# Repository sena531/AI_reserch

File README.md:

# Buck-PFC 研究（長崎大学）

AC100Vrms 50Hz 入力の Buck-PFC（ブリッジレス PFC ＋ 位相シフトフルブリッジ）コンバータの
制御設計・シミュレーション・実機検証をまとめたリポジトリ。
制御器は dsPIC33EP128GS808（MPLAB X + XC16 v1.70）で実装する。

## フォルダ構成

```
buck-pfc-research/
├── simulation/
│   ├── scideam/          # Scideam 回路(.scicir) と制御スクリプト(.sciprc)
│   └── python/           # ACMC ゲイン設計・検証シミュレータと結果波形
├── firmware/
│   ├── BuckPFC.X/        # MPLAB X プロジェクト（ここを MPLAB で開く）
│   ├── src/              # 現行ソース（main_closed_loop.c ほか）
│   └── archive/          # 過去の制御コード（開ループ・DAB 試験・旧閉ループ版）
├── experiments/          # 実機試験結果・手順書・ノイズ対策・フォトカプラ解析
├── hardware/kicad/buck_pfc/  # 最新基板の回路図・PCB・Gerber（KiCad 10）
├── docs/                 # 制御設計メモ・スライド
└── .claude/skills/       # Claude Code 用スキル（電力変換器の制御設計）
```

## 主要ファイル

| 区分 | ファイル | 内容 |
|---|---|---|
| シミュレーション | `simulation/scideam/Buck PFC_closed.scicir` | Buck-PFC 閉ループ回路（最新） |
| | `simulation/scideam/closed_loop_buck_pfc.sciprc` | 上記の制御スクリプト（ファームの元） |
| | `simulation/scideam/bridgeless PFC.scicir` / `closed_loop_bridgeless_pfc.sciprc` | ブリッジレス PFC 単体の ACMC |
| | `simulation/scideam/PhaseShiftFullBridge*.sci*` | 位相シフトフルブリッジ単体 |
| | `simulation/python/pfc_acmc_sim.py` | 平均電流制御のゲイン設計・オフライン検証 |
| | `simulation/python/verify_sciprc_port.py` | .sciprc の逐語移植（転記ミス検出用） |
| 実機 | `firmware/src/main_closed_loop.c` | 現行の閉ループ制御（旧名 `closed_1103.c`） |
| | `experiments/kekka.xlsx` | 実機測定結果 |
| | `experiments/BuckPFC_閉ループ試験_障害解析.pptx` | 閉ループ試験の障害解析 |
| | `experiments/通電手順.html` / `実験前チェックリスト.html` | 実験手順 |
| | `experiments/ACライン_ノイズ対策手順.md` | AC ラインのノイズ対策 |
| | `experiments/photocoupler/` | Vo センシング（フォトカプラ）の実測解析 |
| 資料 | `docs/README_pfc_control.md` | ACMC 制御の設計メモ |

## 使い方

### MPLAB X
1. `firmware/BuckPFC.X` を MPLAB X で開く（デバイス: dsPIC33EP128GS808、コンパイラ: XC16 v1.70）。
2. ビルド対象は `src/main_closed_loop.c` と `src/traps.c`。過去版を試すときは
   `archive/` のファイルをプロジェクトに追加し、`main_closed_loop.c` を除外する。

### Python シミュレーション
```bash
cd simulation/python
python pfc_acmc_sim.py
```

### 文字コードについて
`firmware/` の `.c/.h` はローカルでは Shift-JIS（MPLAB 用）、GitHub 上では UTF-8 で保存される
（`.gitattributes` の `working-tree-encoding` で自動変換）。

## 含めていないもの
先行研究 PDF・修士論文・APEC 投稿資料・参考文献など（著作権・未公開情報のため）、
旧 KiCad プロジェクト、KiCad/MPLAB のバックアップとビルド生成物。
元データは OneDrive の `AI＿研究` フォルダに残っている。

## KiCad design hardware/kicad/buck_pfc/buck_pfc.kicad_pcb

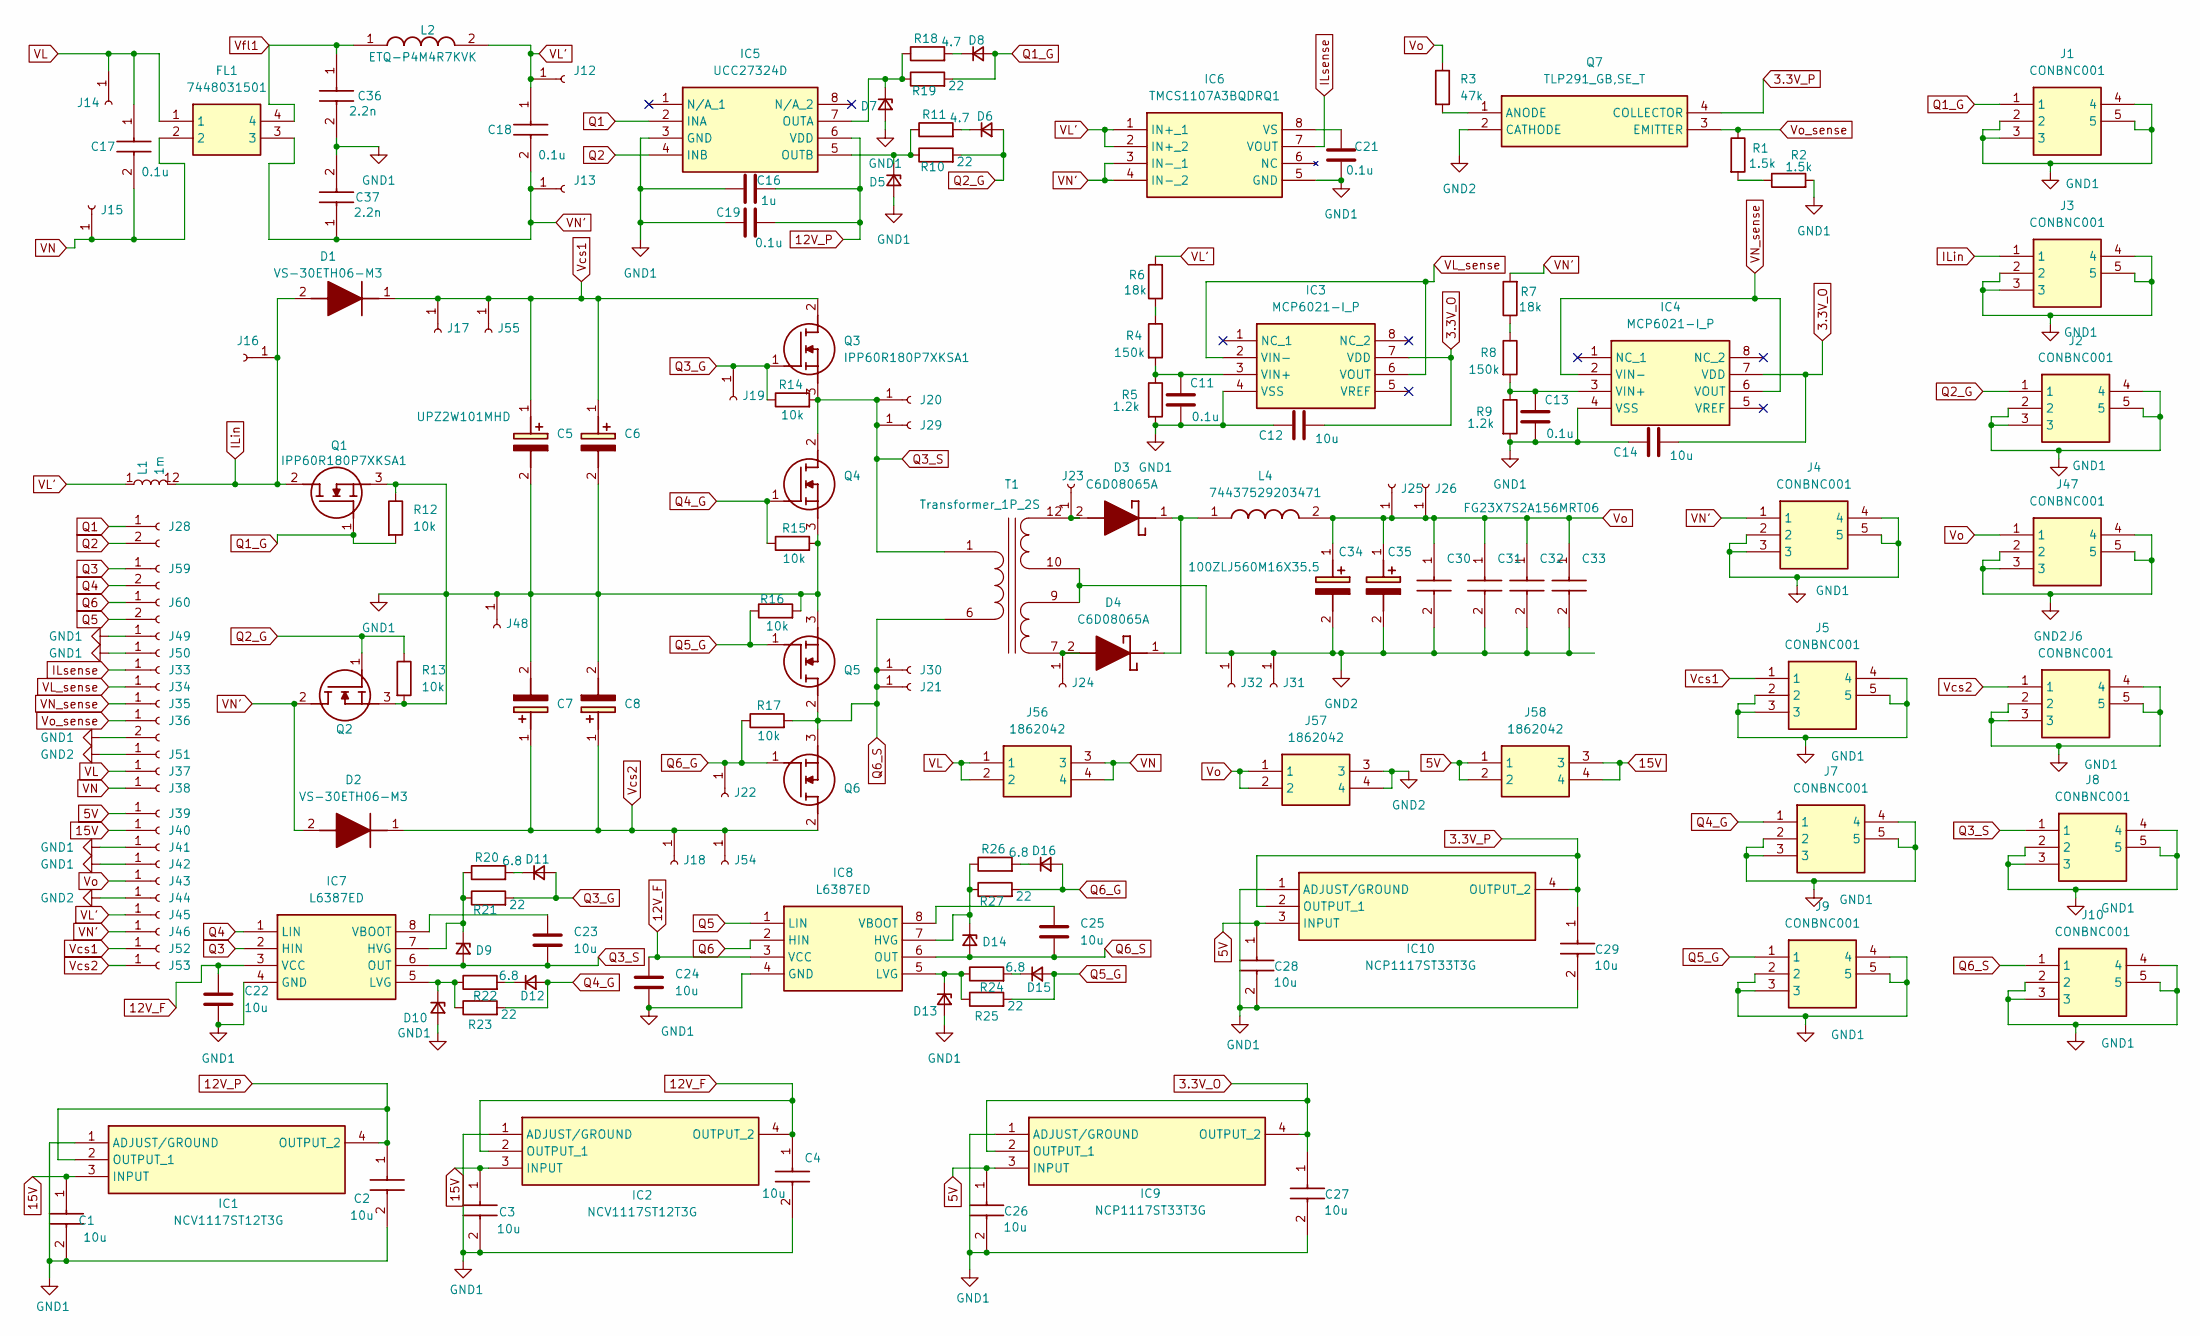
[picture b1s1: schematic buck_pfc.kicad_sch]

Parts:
C1, C2, C3, C4, C26, C27, C28, C29: 10u; CAPC3216X180N; Manufacturer_Part_Number C3216X7R1C106K160AC; Mouser Part Number 810-C3216X7R1C106K
C5, C6, C7, C8: UPZ2W101MHD; CAPPRD750W80D1800H3750; Manufacturer_Part_Number UPZ2W101MHD; Mouser Part Number 647-UPZ2W101MHD
C11, C13, C19, C21: 0.1u; CAPC3216X180N
C12, C14, C22, C23, C24, C25: 10u; CAPC3216X180N
C16: 1u; CAPC3216X180N
C17, C18: 0.1u; B32922P__18_x_5_; Manufacturer_Part_Number B32922P3104K000; Mouser Part Number 871-B32922P3104K000
C30, C31, C32, C33: FG23X7S2A156MRT06; FG23; Manufacturer_Part_Number FG23X7S2A156MRT06; Mouser Part Number 810-FG23X7S2A15MRT06
C34, C35: 100ZLJ560M16X35.5; CAPPRD750W80D1625H3750; Manufacturer_Part_Number 100ZLJ560M16X35.5
C36, C37: 2.2n; C727U222MZVDAA7317; Manufacturer_Part_Number C727U222MZVDAA7317; Mouser Part Number 80-C727U222MZVDA7317
D1, D2: VS-30ETH06-M3; VS30ETH06M3; Manufacturer_Part_Number VS-30ETH06-M3; Mouser Part Number 78-VS-30ETH06-M3
D3, D4: C6D08065A; TO508P470X1004X1995-2P; Manufacturer_Part_Number C6D08065A; Mouser Part Number 941-C6D08065A
D5, D7, D9, D10, D13, D14: D_Zener_Small; DIOM3716X135N
D6, D8, D11, D12, D15, D16: D_Small; SOD3716X135N
FL1: 7448031501; Manufacturer_Part_Number 7448031501; Mouser Part Number 710-7448031501
IC1, IC2: NCV1117ST12T3G; SOT230P700X180-4N; Manufacturer_Part_Number NCV1117ST12T3G; Mouser Part Number 863-NCV1117ST12T3G
IC3, IC4: MCP6021-I_P; DIP794W56P254L946H432Q8N; Manufacturer_Part_Number MCP6021-I/P; Mouser Part Number 579-MCP6021-I/P
IC5: UCC27324D; SOIC127P600X175-8N; Manufacturer_Part_Number UCC27324D; Mouser Part Number 595-UCC27324D
IC6: TMCS1107A3BQDRQ1; SOIC127P600X175-8N; Manufacturer_Part_Number TMCS1107A3BQDRQ1; Mouser Part Number 595-TMCS1107A3BQDRQ1
IC7, IC8: L6387ED; SOIC127P600X175-8N; Manufacturer_Part_Number L6387ED; Mouser Part Number 511-L6387ED
IC9, IC10: NCP1117ST33T3G; SOT230P700X180-4N; Manufacturer_Part_Number NCP1117ST33T3G; Mouser Part Number 863-NCP1117ST33T3G
J1, J2, J3, J4, J5, J6, J7, J8, J9, J10, J47: CONBNC001; Manufacturer_Part_Number CONBNC001; Mouser Part Number 712-CONBNC001
J12, J13, J14, J15, J16, J17, J18, J19, J20, J21, J22, J23, J24, J25, J26, J29, J30, J31, J32, J48, J54, J55: Conn_01x01_Socket; 5013
J28, J36, J59, J60: Conn_01x02_Socket; PinHeader_1x02_P2.54mm_Vertical
J33, J34, J35, J49, J50, J51: Conn_01x01_Socket; PinSocket_1x01_P2.54mm_Vertical
J37, J38, J39, J40, J41, J42, J43, J44, J45, J46, J52, J53: Conn_01x01_Socket; TestPoint_Pad_3.0x3.0mm
J56, J57, J58: 1862042; Manufacturer_Part_Number 1862042; Mouser Part Number 651-1862042
L1: 1m; B65882B0012T001
L2: ETQ-P4M4R7KVK; ETQ-P4M_KVK; Manufacturer_Part_Number ETQ-P4M4R7KVK; Mouser Part Number 667-ETQ-P4M4R7KVK
L4: 74437529203471; 74437529203221; Manufacturer_Part_Number 74437529203471; Mouser Part Number 710-74437529203471
Q1, Q2, Q3, Q4, Q5, Q6: IPP60R180P7XKSA1; TO254P457X1003X2115-3P; Manufacturer_Part_Number IPP60R180P7XKSA1; Mouser Part Number 726-IPP60R180P7XKSA1
Q7: TLP291_GB,SE_T; SOIC127P700X230-4N; Manufacturer_Part_Number TLP291(GB,SE(T
R1, R2: 1.5k; RESC3116X65N
R3: 47k; RESC3116X65N
R4, R8: 150k; RESC3116X65N
R5, R9: 1.2k; RESC3116X65N
R6, R7: 18k; RESC3116X65N
R10, R19, R21, R23, R25, R27: 22; RESC3116X65N
R11, R18: 4.7; RESC3116X65N
R12, R13, R14, R15, R16, R17: 10k; RESC3116X65N
R20, R22, R24, R26: 6.8; RESC3116X65N
T1: Transformer_1P_2S; B65882B0012T001

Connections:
3.3V_O: C12.2, C14.2, C27.1, IC3.7 (VDD), IC4.7 (VDD), IC9.2 (OUTPUT_1), IC9.4 (OUTPUT_2)
3.3V_P: C29.1, IC10.2 (OUTPUT_1), IC10.4 (OUTPUT_2), Q7.4 (COLLECTOR)
5V: C26.1, C28.1, IC9.3 (INPUT), IC10.3 (INPUT), J39.1 (Pin_1_1), J58.1, J58.2
12V_F: C4.1, C22.1, C24.1, IC2.2 (OUTPUT_1), IC2.4 (OUTPUT_2), IC7.3 (VCC), IC8.3 (VCC)
12V_P: C2.1, C16.2, C19.2, IC1.2 (OUTPUT_1), IC1.4 (OUTPUT_2), IC5.6 (VDD)
15V: C1.1, C3.1, IC1.3 (INPUT), IC2.3 (INPUT), J40.1 (Pin_1_1), J58.3, J58.4
GND1: C1.2, C2.2, C3.2, C4.2, C5.2 (-), C6.2 (-), C7.2 (-), C8.2 (-), C11.2, C12.1, C13.2, C14.1, C16.1, C19.1, C21.1, C22.2, C24.2, C26.2, C27.2, C28.2, C29.2, C36.2, C37.2, D5.2 (A), D7.2 (A), D10.2 (A), D13.2 (A), IC1.1 (ADJUST/GROUND), IC2.1 (ADJUST/GROUND), IC3.4 (VSS), IC4.4 (VSS), IC5.3 (GND), IC6.5 (GND), IC7.4 (GND), IC8.4 (GND), IC9.1 (ADJUST/GROUND), IC10.1 (ADJUST/GROUND), J1.2, J1.3, J1.4, J1.5, J2.2, J2.3, J2.4, J2.5, J3.2, J3.3, J3.4, J3.5, J4.2, J4.3, J4.4, J4.5, J5.2, J5.3, J5.4, J5.5, J6.2, J6.3, J6.4, J6.5, J7.2, J7.3, J7.4, J7.5, J8.2, J8.3, J8.4, J8.5, J9.2, J9.3, J9.4, J9.5, J10.2, J10.3, J10.4, J10.5, J36.2, J41.1 (Pin_1_1), J42.1 (Pin_1_1), J48.1 (Pin_1_1), J49.1 (Pin_1_1), J50.1 (Pin_1_1), Q1.3 (S), Q2.3 (S), Q4.3 (S), Q5.3 (S), R2.2, R5.2, R9.2, R12.1, R13.2, R15.2, R16.2
GND2: C30.2, C31.2, C32.2, C33.2, C34.2 (-), C35.2 (-), J31.1 (Pin_1_1), J32.1 (Pin_1_1), J44.1 (Pin_1_1), J47.2, J47.3, J47.4, J47.5, J51.1 (Pin_1_1), J57.3, J57.4, Q7.2 (CATHODE), T1.9 (SC), T1.10 (SB)
ILin: D1.2 (A), J3.1, J16.1 (Pin_1_1), L1.12, Q1.2 (D)
ILsense: IC6.7 (VOUT), J33.1 (Pin_1_1)
unnamed: D3.2 (A), J23.1 (Pin_1_1), T1.12 (SA)
unnamed: D3.1 (K), D4.1 (K), L4.1
unnamed: D4.2 (A), J24.1 (Pin_1_1), T1.7 (SD)
unnamed: D5.1 (K), IC5.5 (OUTB), R10.1, R11.1
unnamed: D6.1 (K), R11.2
unnamed: D7.1 (K), IC5.7 (OUTA), R18.1, R19.1
unnamed: D8.1 (K), R18.2
unnamed: D9.1 (K), IC7.7 (HVG), R20.1, R21.1
unnamed: D10.1 (K), IC7.5 (LVG), R22.1, R23.1
unnamed: D11.1 (K), R20.2
unnamed: D12.1 (K), R22.2
unnamed: D13.1 (K), IC8.5 (LVG), R24.1, R25.1
unnamed: D14.1 (K), IC8.7 (HVG), R26.1, R27.1
unnamed: D15.1 (K), R24.2
unnamed: D16.1 (K), R26.2
unnamed: C11.1, IC3.3 (VIN+), R4.2, R5.1
unnamed: C13.1, IC4.3 (VIN+), R8.2, R9.1
unnamed: C21.2, IC6.8 (VS)
unnamed: C23.1, IC7.8 (VBOOT)
unnamed: C25.1, IC8.8 (VBOOT)
unnamed: Q7.1 (ANODE), R3.2
unnamed: R1.2, R2.1
unnamed: R4.1, R6.1
unnamed: R7.1, R8.1
Q1: IC5.2 (INA), J28.1
Q1_G: D8.2 (A), J1.1, Q1.1 (G), R12.2, R19.2
Q2: IC5.4 (INB), J28.2
Q2_G: D6.2 (A), J2.1, Q2.1 (G), R10.2, R13.1
Q3: IC7.2 (HIN), J59.1
Q3_G: D11.2 (A), J19.1 (Pin_1_1), Q3.1 (G), R14.1, R21.2
Q3_S: C23.2, D9.2 (A), IC7.6 (OUT), J8.1, J20.1 (Pin_1_1), J29.1 (Pin_1_1), Q3.3 (S), Q4.2 (D), R14.2, T1.1 (AA)
Q4: IC7.1 (LIN), J59.2
Q4_G: D12.2 (A), J7.1, Q4.1 (G), R15.1, R23.2
Q5: IC8.1 (LIN), J60.2
Q5_G: D15.2 (A), J9.1, Q5.1 (G), R16.1, R25.2
Q6: IC8.2 (HIN), J60.1
Q6_G: D16.2 (A), J22.1 (Pin_1_1), Q6.1 (G), R17.1, R27.2
Q6_S: C25.2, D14.2 (A), IC8.6 (OUT), J10.1, J21.1 (Pin_1_1), J30.1 (Pin_1_1), Q5.2 (D), Q6.3 (S), R17.2, T1.6 (AB)
VL: C17.1, FL1.1, J14.1 (Pin_1_1), J37.1 (Pin_1_1), J56.1, J56.2
VL': C18.1, IC6.1 (IN+_1), IC6.2 (IN+_2), J12.1 (Pin_1_1), J45.1 (Pin_1_1), L1.1, L2.2, R6.2
VL_sense: IC3.2 (VIN-), IC3.6 (VOUT), J34.1 (Pin_1_1)
VN: C17.2, FL1.2, J15.1 (Pin_1_1), J38.1 (Pin_1_1), J56.3, J56.4
VN': C18.2, C37.1, D2.2 (A), FL1.3, IC6.3 (IN-_1), IC6.4 (IN-_2), J4.1, J13.1 (Pin_1_1), J46.1 (Pin_1_1), Q2.2 (D), R7.2
VN_sense: IC4.2 (VIN-), IC4.6 (VOUT), J35.1 (Pin_1_1)
Vcs1: C5.1 (+), C6.1 (+), D1.1 (K), J5.1, J17.1 (Pin_1_1), J52.1 (Pin_1_1), J55.1 (Pin_1_1), Q3.2 (D)
Vcs2: C7.1 (+), C8.1 (+), D2.1 (K), J6.1, J18.1 (Pin_1_1), J53.1 (Pin_1_1), J54.1 (Pin_1_1), Q6.2 (D)
Vfl1: C36.1, FL1.4, L2.1
Vo: C30.1, C31.1, C32.1, C33.1, C34.1 (+), C35.1 (+), J25.1 (Pin_1_1), J26.1 (Pin_1_1), J43.1 (Pin_1_1), J47.1, J57.1, J57.2, L4.2, R3.1
Vo_sense: J36.1, Q7.3 (EMITTER), R1.1

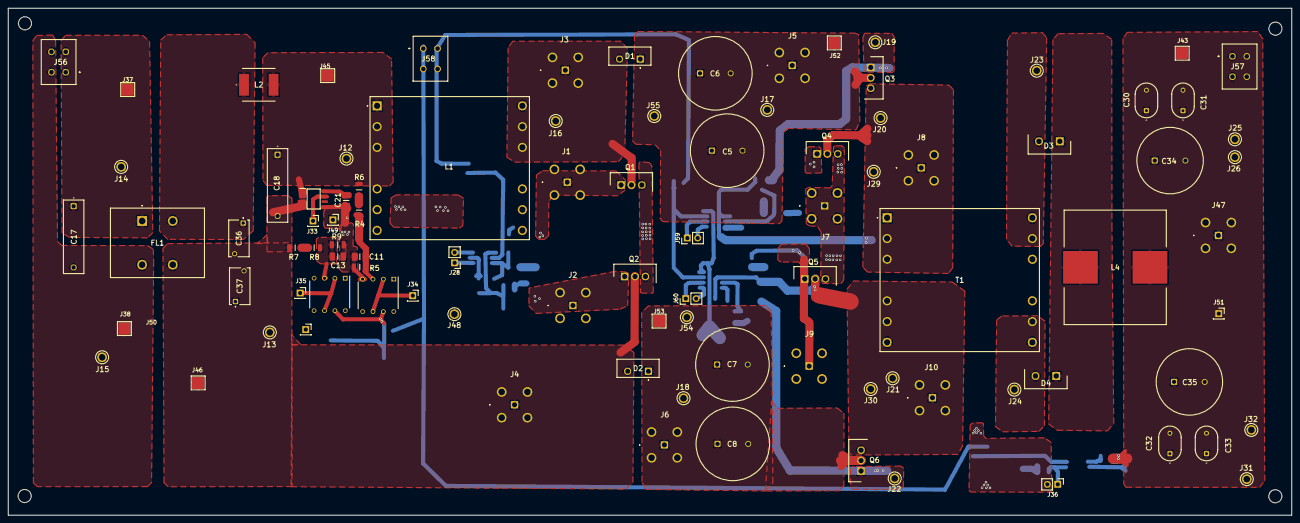
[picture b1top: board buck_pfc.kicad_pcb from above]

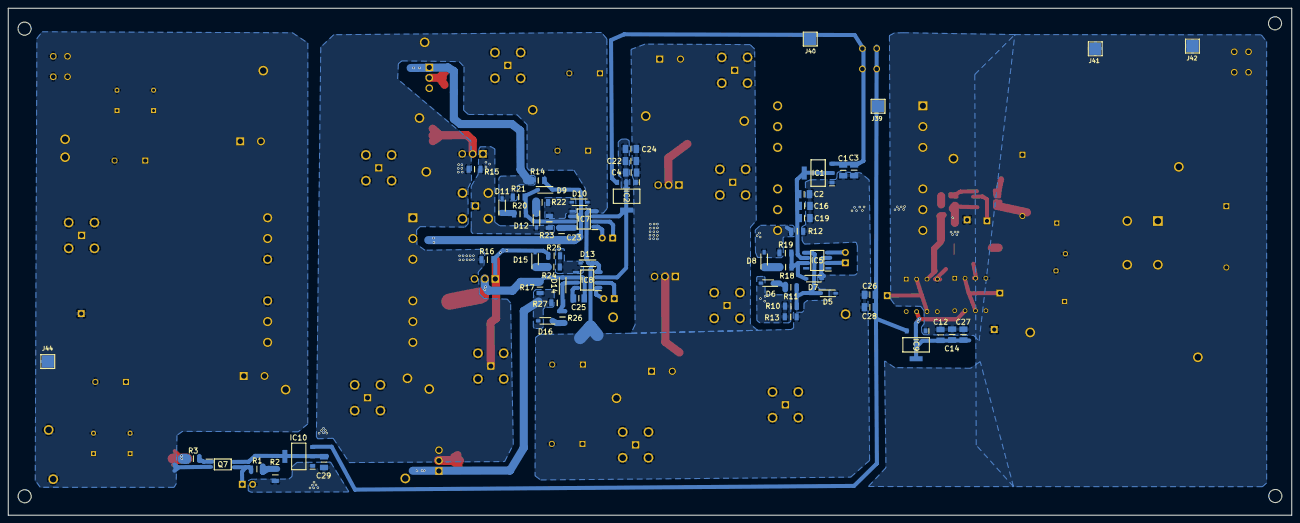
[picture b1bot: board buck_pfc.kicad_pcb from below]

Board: 2 copper layers, 314.0 x 124.0 mm, 156 parts (62 on the bottom side), 59 nets.
